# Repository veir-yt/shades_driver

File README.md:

# Shades Motor Driver Project

Contains the following design files:
- CAD (FreeCAD)
- PCB (KiCAD)
- Firmware (Arduino Nano)
- Software (ESP32)

## Feel free to steal and improve :)

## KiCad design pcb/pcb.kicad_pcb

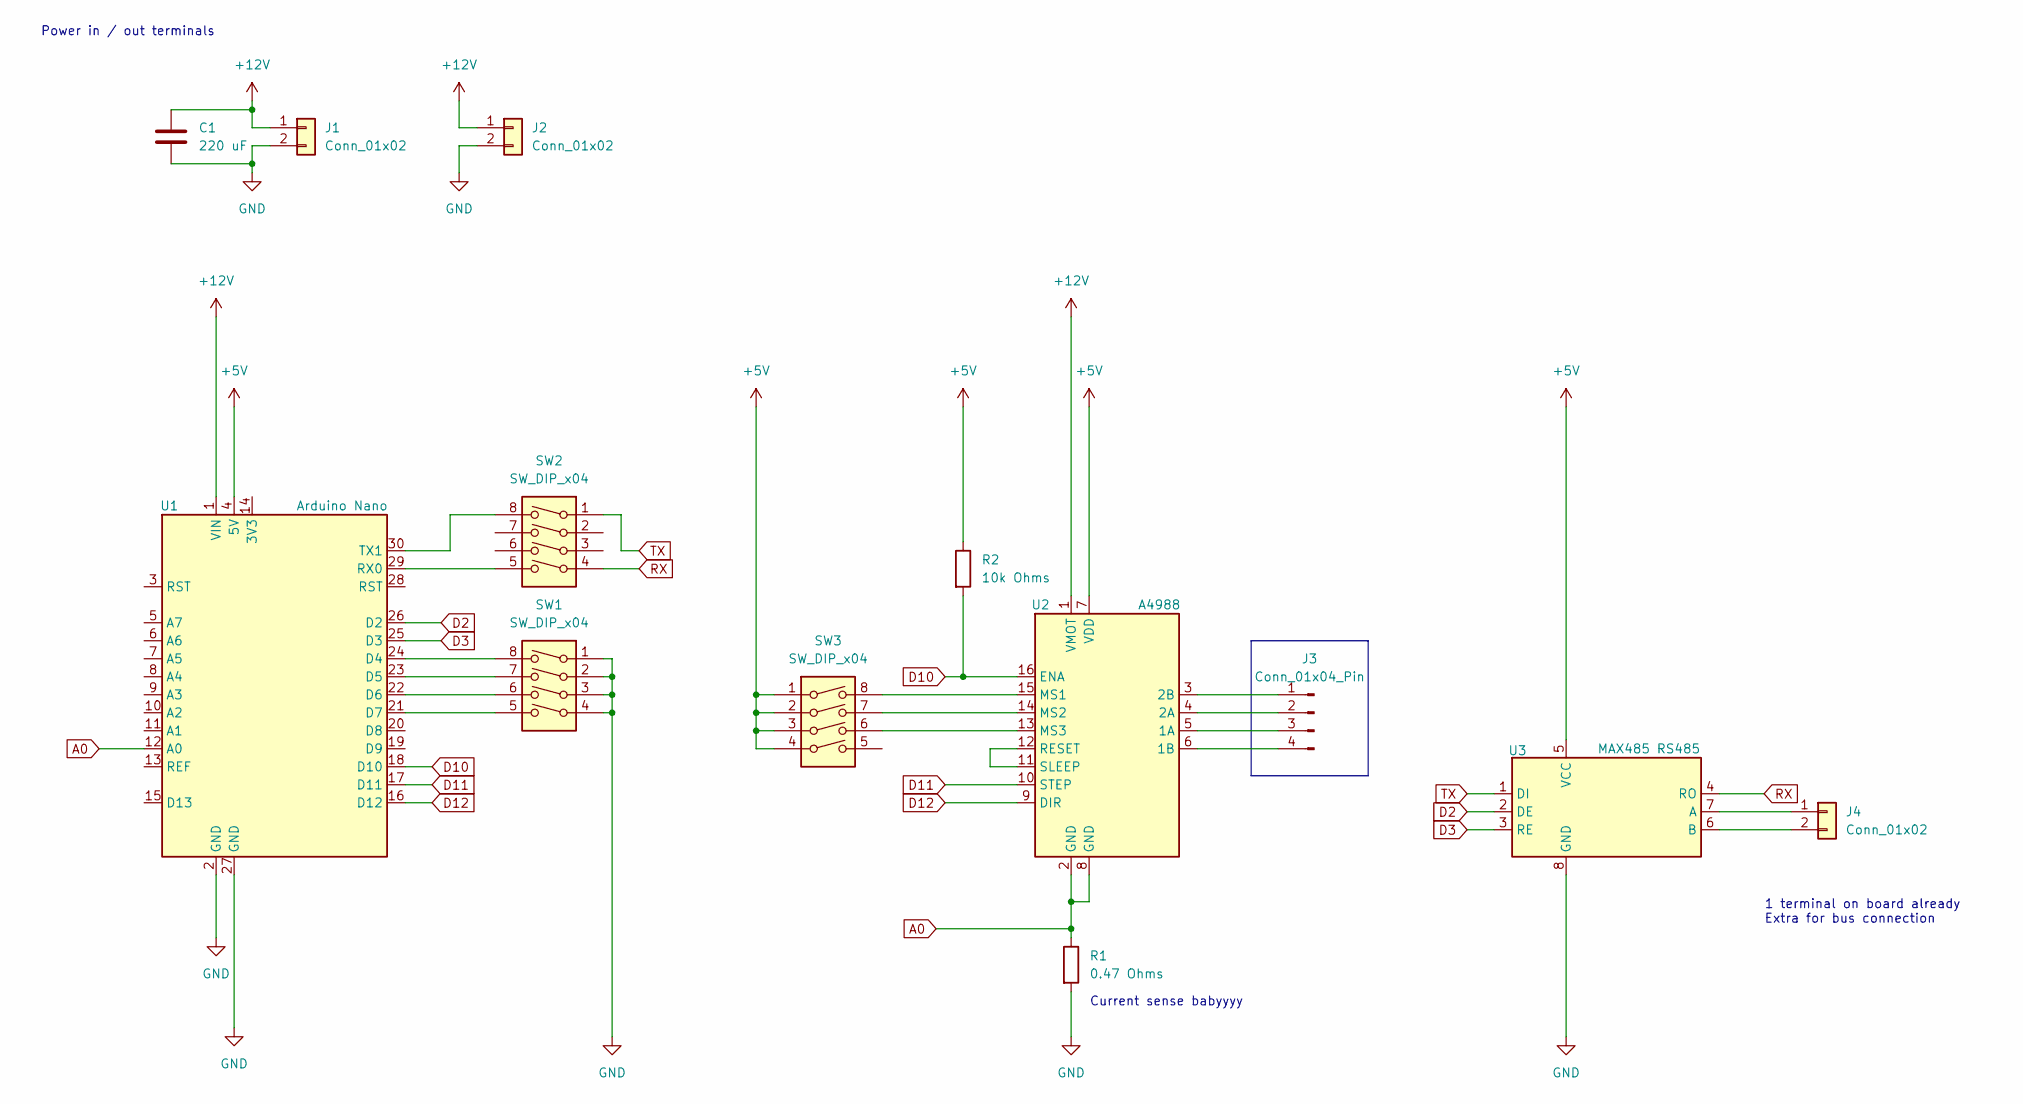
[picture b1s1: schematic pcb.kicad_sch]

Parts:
C1: 220 uF; CP_Radial_D6.3mm_P2.50mm
J1, J2, J4: Conn_01x02; TerminalBlock_Phoenix_MKDS-1,5-2-5.08_1x02_P5.08mm_Horizont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
J3: Conn_01x04_Pin; PinHeader_1x04_P2.54mm_Vertical
R1: 0.47 Ohms; R_Axial_Power_L25.0mm_W9.0mm_P30.48mm
R2: 10k Ohms; R_Axial_DIN0207_L6.3mm_D2.5mm_P10.16mm_Horizontal
SW1, SW2, SW3: SW_DIP_x04; DIP-8_W7.62mm
U1: Arduino Nano
U2: A4988
U3: MAX485 RS485

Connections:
+5V: R2.1, SW3.1, SW3.2, SW3.3, SW3.4, U1.4 (5V), U2.7 (VDD), U3.5 (VCC)
+12V: C1.1, J1.1, J2.1, U1.1 (VIN), U2.1 (VMOT)
A0: R1.1, U1.12 (A0), U2.2 (GND), U2.8 (GND)
D2: U1.26 (D2), U3.2 (DE)
D3: U1.25 (D3), U3.3 (RE)
D10: R2.2, U1.18 (D10), U2.16 (ENA)
D11: U1.17 (D11), U2.10 (STEP)
D12: U1.16 (D12), U2.9 (DIR)
GND: C1.2, J1.2, J2.2, R1.2, SW1.1, SW1.2, SW1.3, SW1.4, U1.2 (GND), U1.27 (GND), U3.8 (GND)
unnamed: J3.1, U2.3 (2B)
unnamed: J3.2, U2.4 (2A)
unnamed: J3.3, U2.5 (1A)
unnamed: J3.4, U2.6 (1B)
unnamed: J4.1, U3.7 (A)
unnamed: J4.2, U3.6 (B)
unnamed: SW1.8, U1.24 (D4)
unnamed: SW1.7, U1.23 (D5)
unnamed: SW1.6, U1.22 (D6)
unnamed: SW1.5, U1.21 (D7)
unnamed: SW2.5, U1.29 (RX0)
unnamed: SW2.8, U1.30 (TX1)
unnamed: SW3.8, U2.15 (MS1)
unnamed: SW3.7, U2.14 (MS2)
unnamed: SW3.6, U2.13 (MS3)
unnamed: U2.11 (SLEEP), U2.12 (RESET)
RX: SW2.4, U3.4 (RO)
TX: SW2.1, U3.1 (DI)

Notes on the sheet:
1 terminal on board already Extra for bus connection
Power in / out terminals
Current sense babyyyy

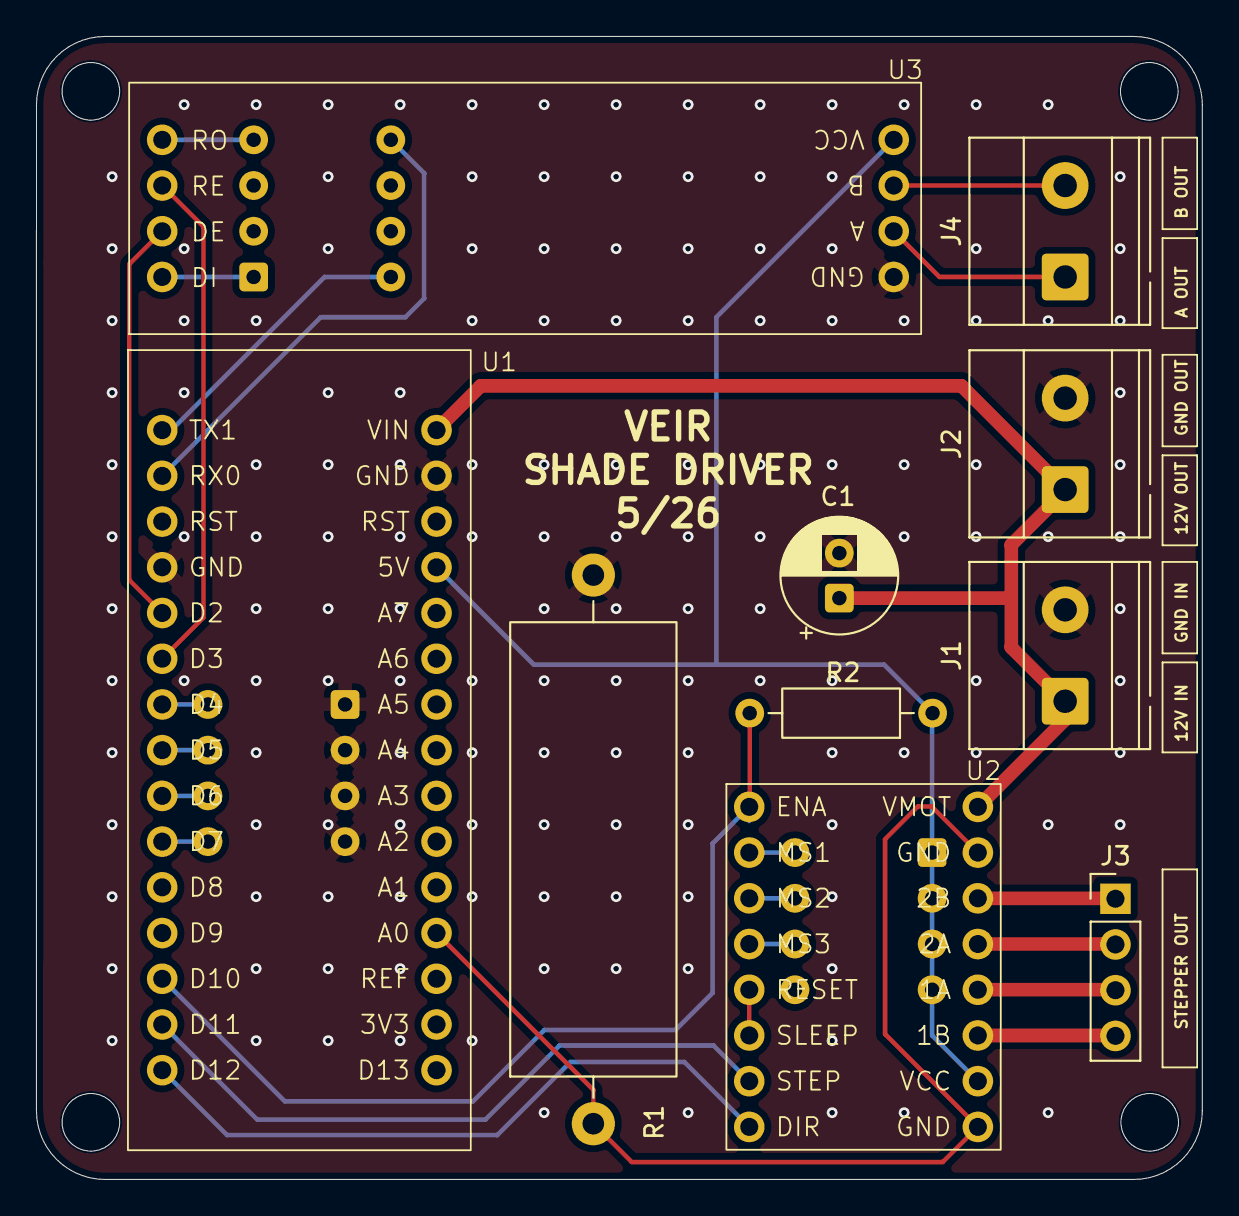
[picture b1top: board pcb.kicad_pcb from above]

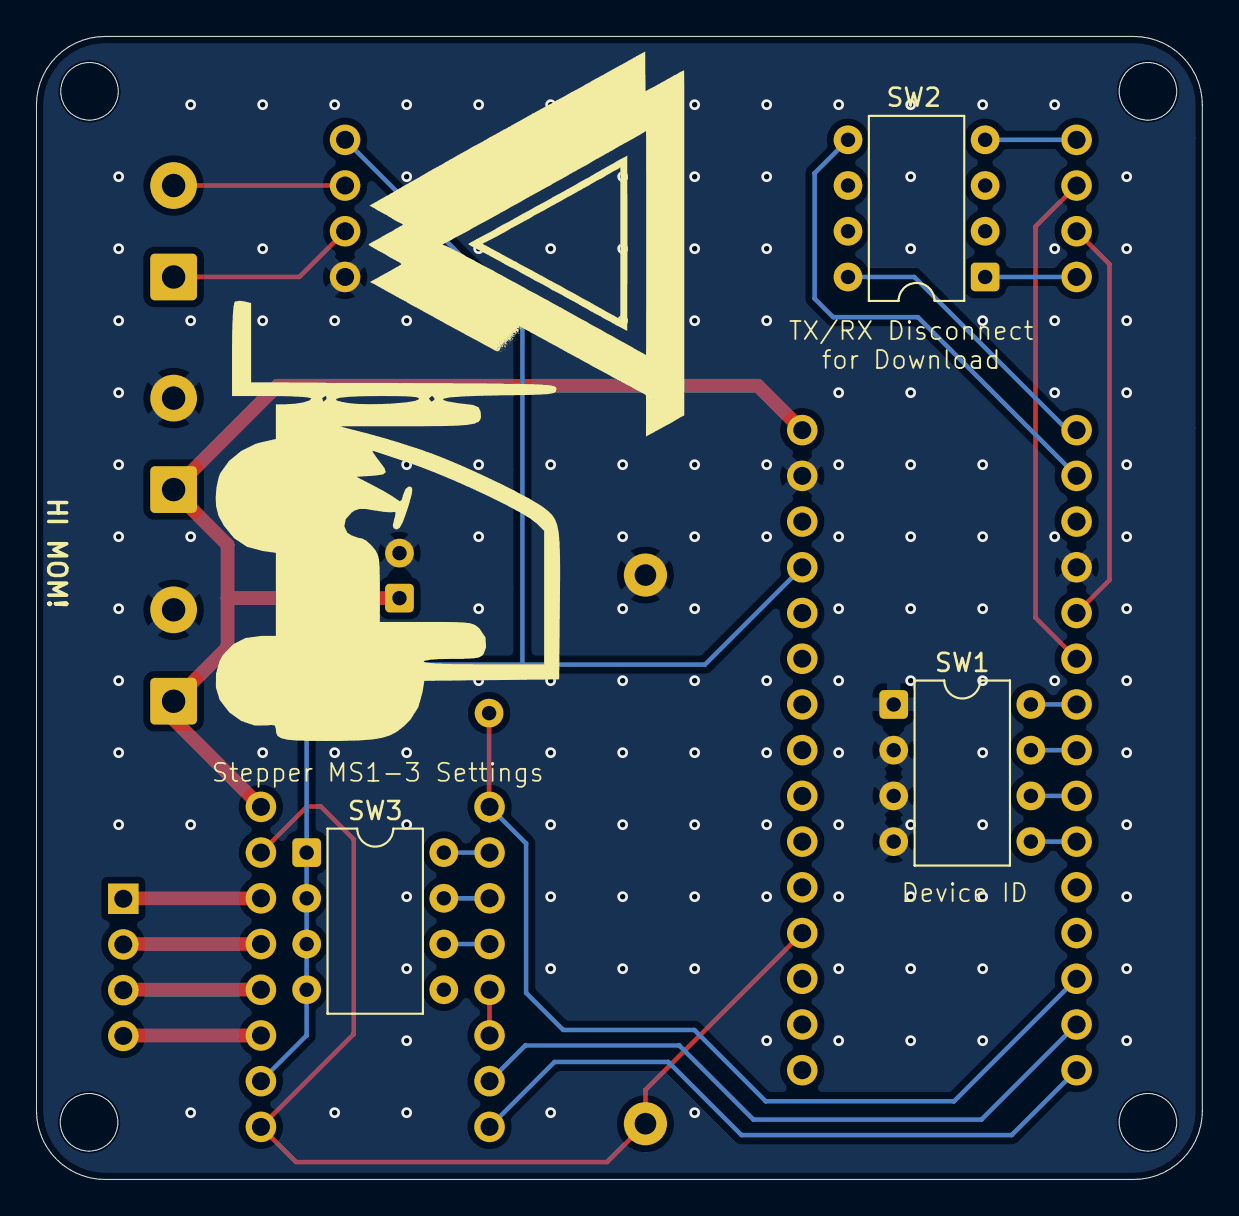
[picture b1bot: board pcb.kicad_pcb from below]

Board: 2 copper layers, 64.8 x 63.5 mm, 13 parts (3 on the bottom side), 27 nets.
